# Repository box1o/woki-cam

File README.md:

# woki cam

modular infrared camera for optical tracking of retroreflective markers.

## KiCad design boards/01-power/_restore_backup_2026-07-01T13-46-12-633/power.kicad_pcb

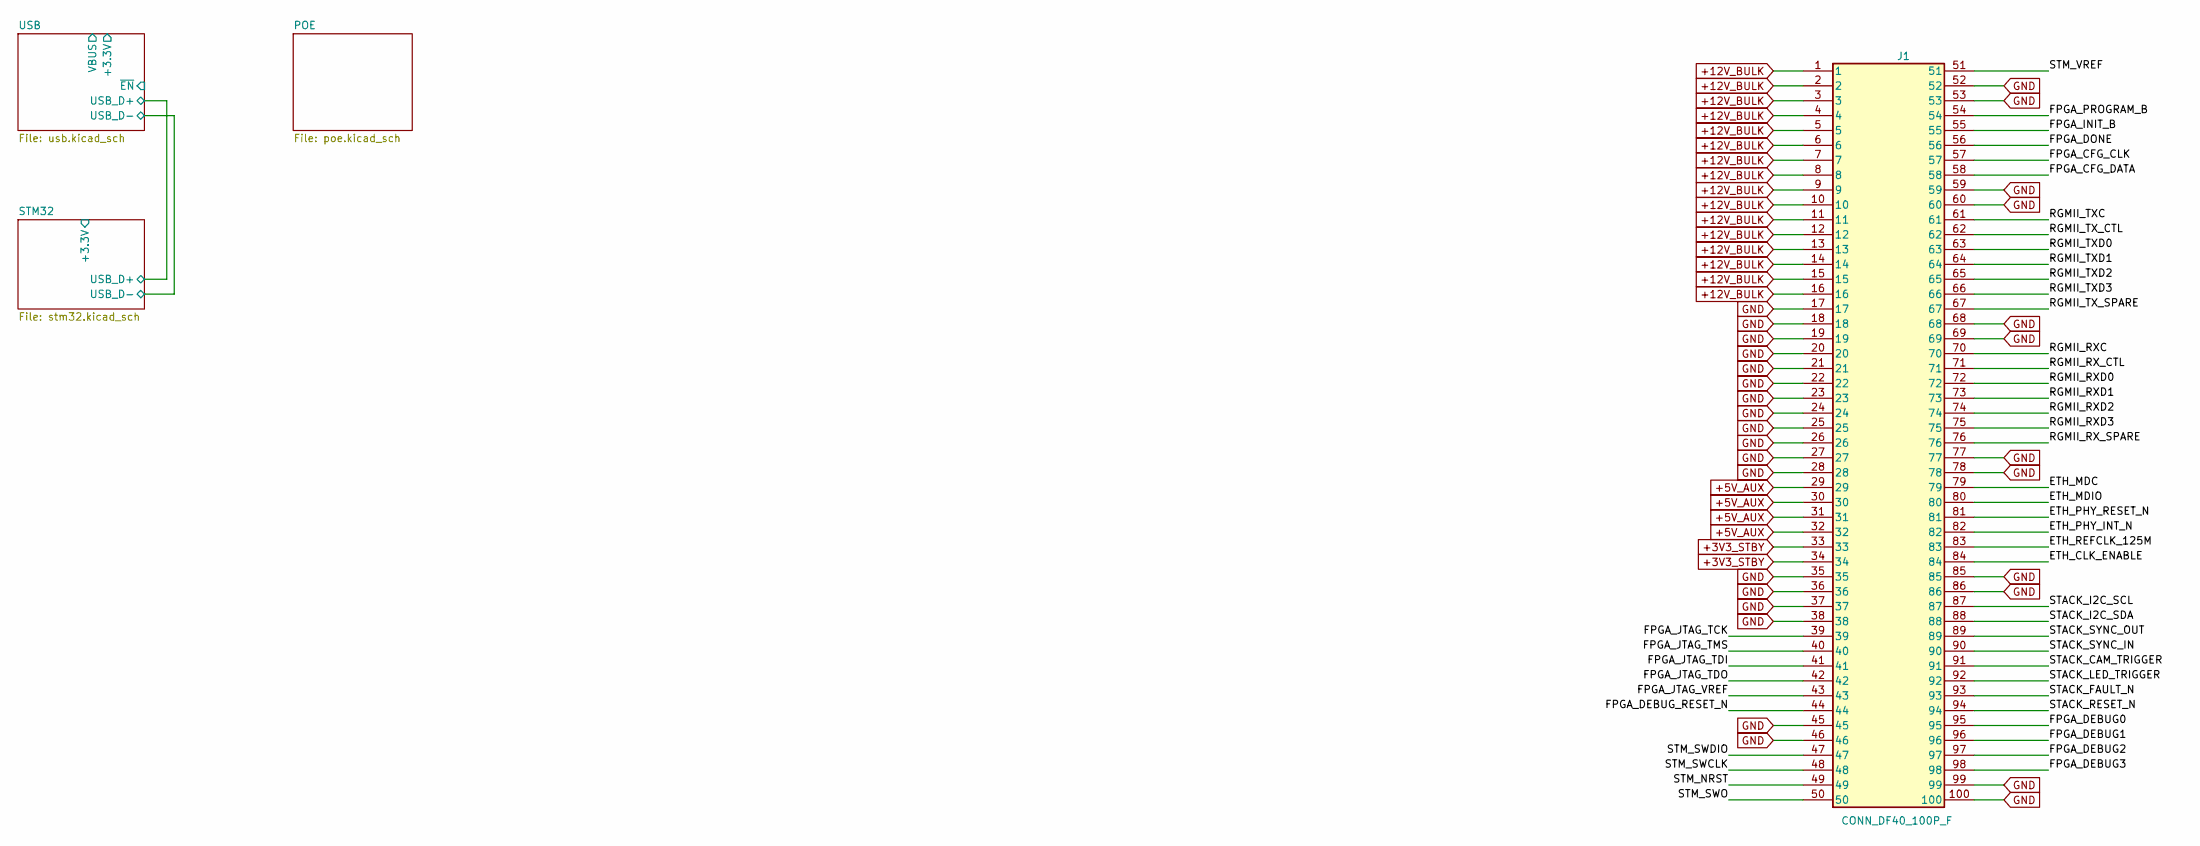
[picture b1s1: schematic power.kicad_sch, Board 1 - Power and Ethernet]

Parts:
J1: CONN_DF40_100P_F

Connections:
+3V3_STBY: J1.33, J1.34
+5V_AUX: J1.29, J1.30, J1.31, J1.32
+12V_BULK: J1.1, J1.2, J1.3, J1.4, J1.5, J1.6, J1.7, J1.8, J1.9, J1.10, J1.11, J1.12, J1.13, J1.14, J1.15, J1.16
/ETH_CLK_ENABLE: J1.84
/ETH_MDC: J1.79
/ETH_MDIO: J1.80
/ETH_PHY_INT_N: J1.82
/ETH_PHY_RESET_N: J1.81
/ETH_REFCLK_125M: J1.83
/FPGA_CFG_CLK: J1.57
/FPGA_CFG_DATA: J1.58
/FPGA_DEBUG0: J1.95
/FPGA_DEBUG1: J1.96
/FPGA_DEBUG2: J1.97
/FPGA_DEBUG3: J1.98
/FPGA_DEBUG_RESET_N: J1.44
/FPGA_DONE: J1.56
/FPGA_INIT_B: J1.55
/FPGA_JTAG_TCK: J1.39
/FPGA_JTAG_TDI: J1.41
/FPGA_JTAG_TDO: J1.42
/FPGA_JTAG_TMS: J1.40
/FPGA_JTAG_VREF: J1.43
/FPGA_PROGRAM_B: J1.54
/RGMII_RXC: J1.70
/RGMII_RXD0: J1.72
/RGMII_RXD1: J1.73
/RGMII_RXD2: J1.74
/RGMII_RXD3: J1.75
/RGMII_RX_CTL: J1.71
/RGMII_RX_SPARE: J1.76
/RGMII_TXC: J1.61
/RGMII_TXD0: J1.63
/RGMII_TXD1: J1.64
/RGMII_TXD2: J1.65
/RGMII_TXD3: J1.66
/RGMII_TX_CTL: J1.62
/RGMII_TX_SPARE: J1.67
/STACK_CAM_TRIGGER: J1.91
/STACK_FAULT_N: J1.93
/STACK_I2C_SCL: J1.87
/STACK_I2C_SDA: J1.88
/STACK_LED_TRIGGER: J1.92
/STACK_RESET_N: J1.94
/STACK_SYNC_IN: J1.90
/STACK_SYNC_OUT: J1.89
/STM_NRST: J1.49
/STM_SWCLK: J1.48
/STM_SWDIO: J1.47
/STM_SWO: J1.50
/STM_VREF: J1.51
GND: J1.17, J1.18, J1.19, J1.20, J1.21, J1.22, J1.23, J1.24, J1.25, J1.26, J1.27, J1.28, J1.35, J1.36, J1.37, J1.38, J1.45, J1.46, J1.52, J1.53, J1.59, J1.60, J1.68, J1.69, J1.77, J1.78, J1.85, J1.86, J1.99, J1.100; also elsewhere on the board

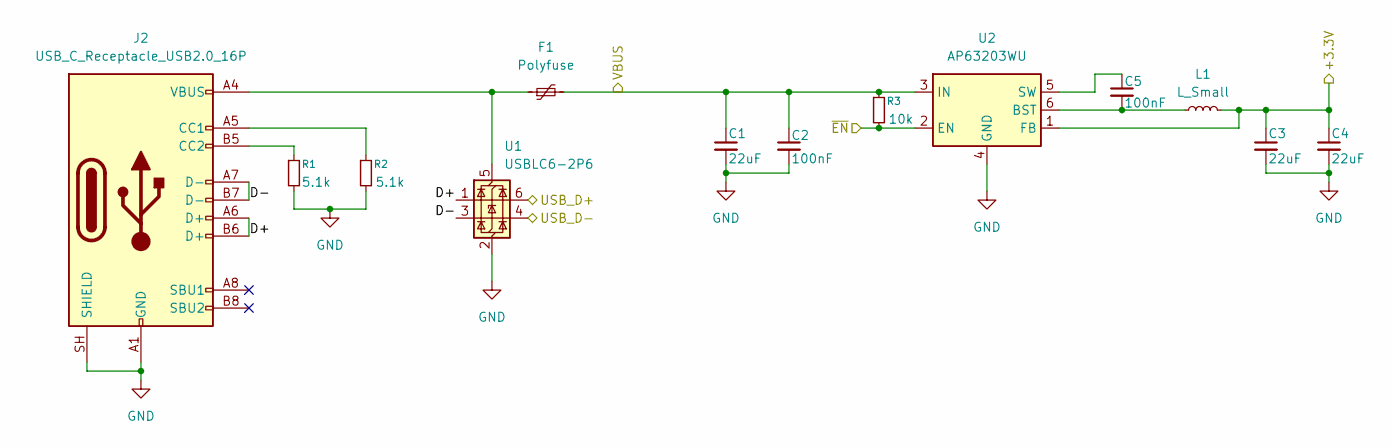
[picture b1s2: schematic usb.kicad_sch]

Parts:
C1, C3, C4: 22uF; C_0603_1608Metric
C2, C5: 100nF; C_0603_1608Metric
F1: Polyfuse; Fuse_0603_1608Metric
J2: USB_C_Receptacle_USB2.0_16P; CONN_USB_C_M
L1: L_Small; L_APV_ANR3012
R1, R2: 5.1k; R_0603_1608Metric
R3: 10k; R_0603_1608Metric
U1: USBLC6-2P6; SOT-666
U2: AP63203WU; TSOT-23-6

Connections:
/STM32/USB_D+: U1.6 (I/O1); also elsewhere on the board
/STM32/USB_D-: U1.4 (I/O2); also elsewhere on the board
/USB/+3.3V: C3.1, C4.1, L1.2, U2.1 (FB)
/USB/D+: J2.A6 (D+), J2.B6 (D+), U1.1 (I/O1)
/USB/D-: J2.A7 (D-), J2.B7 (D-), U1.3 (I/O2)
/USB/VBUS: C1.1, C2.1, F1.2, R3.1, U2.3 (IN)
/USB/~EN: R3.2, U2.2 (EN)
GND: C1.2, C2.2, C3.2, C4.2, J2.A1 (GND), J2.A12 (GND), J2.B1 (GND), J2.B12 (GND), J2.SH (SHIELD), R1.2, R2.2, U1.2 (GND), U2.4 (GND); also elsewhere on the board
unnamed: J2.A5 (CC1), R2.1
unnamed: J2.B5 (CC2), R1.1
unnamed: F1.1, J2.A4 (VBUS), J2.A9 (VBUS), J2.B4 (VBUS), J2.B9 (VBUS), U1.5 (VBUS)
unnamed: C5.2, L1.1, U2.6 (BST)
unnamed: C5.1, U2.5 (SW)

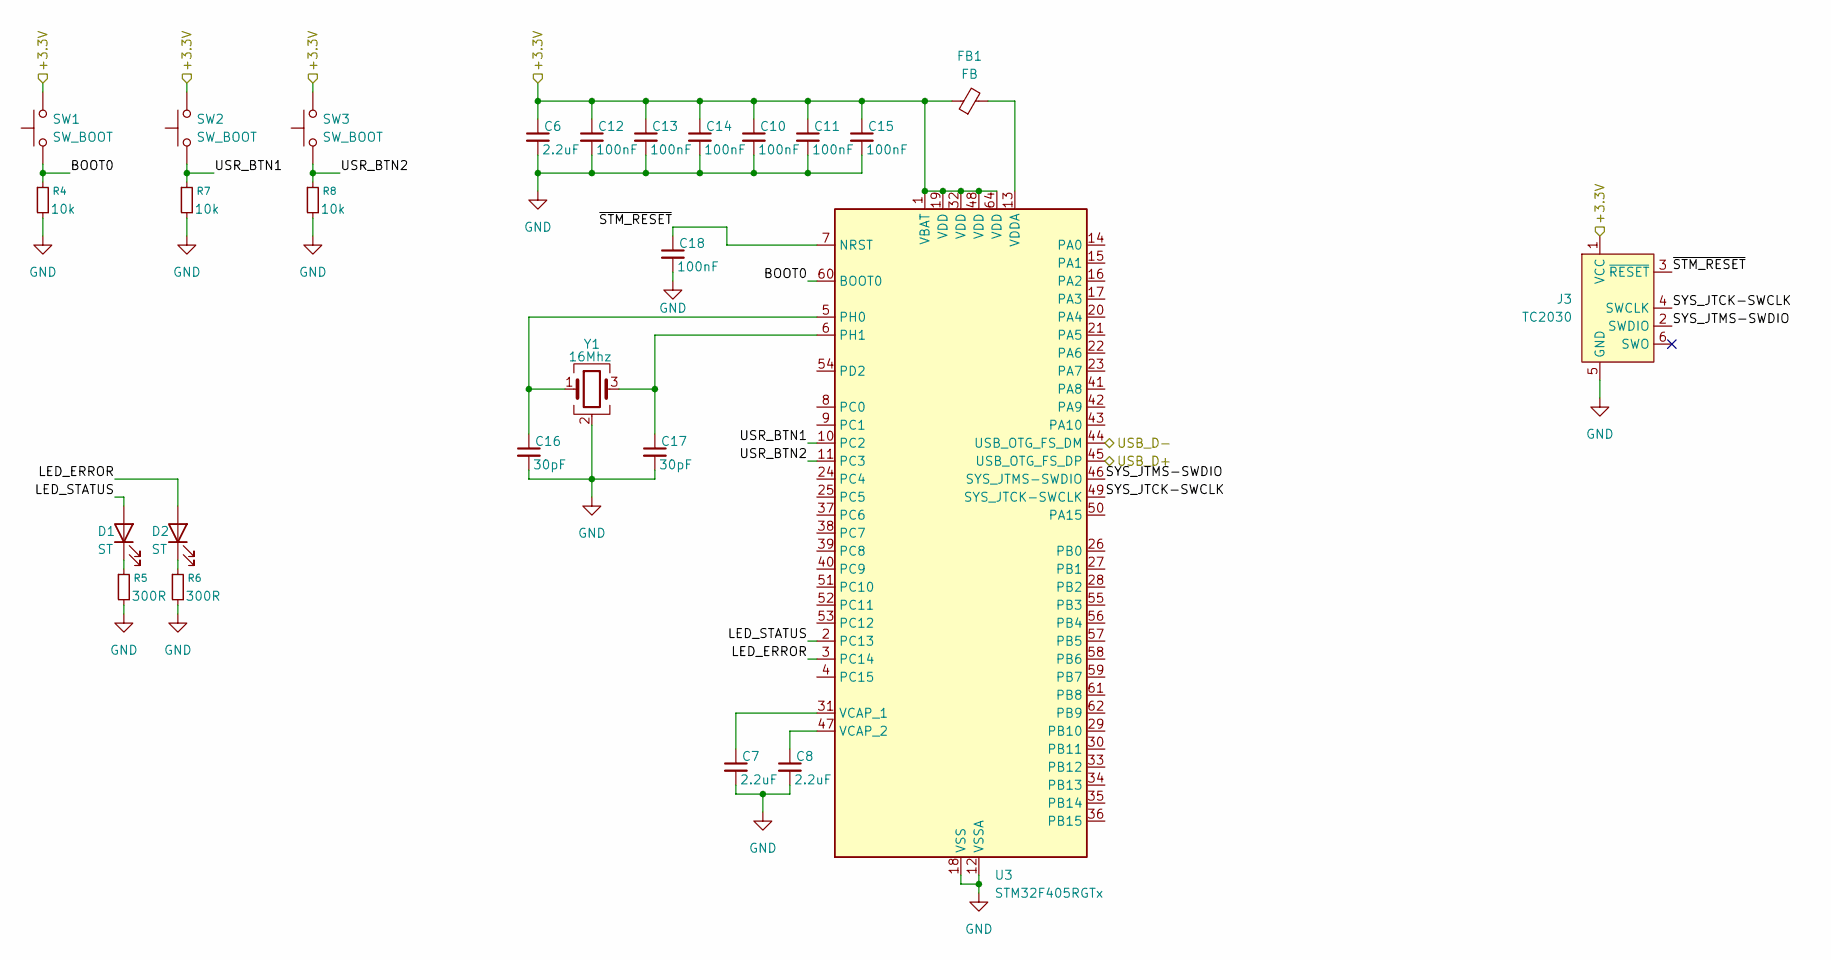
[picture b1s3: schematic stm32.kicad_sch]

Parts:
C6, C7, C8: 2.2uF; C_0603_1608Metric
C10, C11, C12, C13, C14, C15, C18: 100nF; C_0603_1608Metric
C16, C17: 30pF; C_0603_1608Metric
D1, D2: ST; LED_0603_1608Metric
FB1: FB; L_0603_1608Metric
J3: TC2030; Tag-Connect_TC2030-IDC-FP_2x03_P1.27mm_Vertical
R4, R7, R8: 10k; R_0603_1608Metric
R5, R6: 300R; R_0603_1608Metric
SW1, SW2, SW3: SW_BOOT; SW_B3U_1000P
U3: STM32F405RGTx; LQFP-64_10x10mm_P0.5mm
Y1: 16Mhz; Crystal_SMD_3225-4Pin_3.2x2.5mm

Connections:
/STM32/+3.3V: C6.1, C10.1, C11.1, C12.1, C13.1, C14.1, C15.1, FB1.1, J3.1 (VCC), SW1.2, SW2.2, SW3.2, U3.1 (VBAT), U3.19 (VDD), U3.32 (VDD), U3.48 (VDD), U3.64 (VDD)
/STM32/BOOT0: R4.1, SW1.1, U3.60 (BOOT0)
/STM32/LED_ERROR: D2.2 (A), U3.3 (PC14)
/STM32/LED_STATUS: D1.2 (A), U3.2 (PC13)
/STM32/SYS_JTCK-SWCLK: J3.4 (SWCLK), U3.49 (SYS_JTCK-SWCLK)
/STM32/SYS_JTMS-SWDIO: J3.2 (SWDIO), U3.46 (SYS_JTMS-SWDIO)
/STM32/USB_D+: U3.45 (USB_OTG_FS_DP); also elsewhere on the board
/STM32/USB_D-: U3.44 (USB_OTG_FS_DM); also elsewhere on the board
/STM32/USR_BTN1: R7.1, SW2.1, U3.10 (PC2)
/STM32/USR_BTN2: R8.1, SW3.1, U3.11 (PC3)
/STM32/~STM_RESET: C18.1, J3.3 (~RESET), U3.7 (NRST)
GND: C6.2, C7.2, C8.2, C10.2, C11.2, C12.2, C13.2, C14.2, C15.2, C16.2, C17.2, C18.2, J3.5 (GND), R4.2, R5.2, R6.2, R7.2, R8.2, U3.12 (VSSA), U3.18 (VSS), U3.63 (VSS), Y1.2 (G), Y1.4 (G); also elsewhere on the board
unnamed: D1.1 (K), R5.1
unnamed: D2.1 (K), R6.1
unnamed: C16.1, U3.5 (PH0), Y1.1
unnamed: C17.1, U3.6 (PH1), Y1.3
unnamed: C7.1, U3.31 (VCAP_1)
unnamed: C8.1, U3.47 (VCAP_2)
unnamed: FB1.2, U3.13 (VDDA)

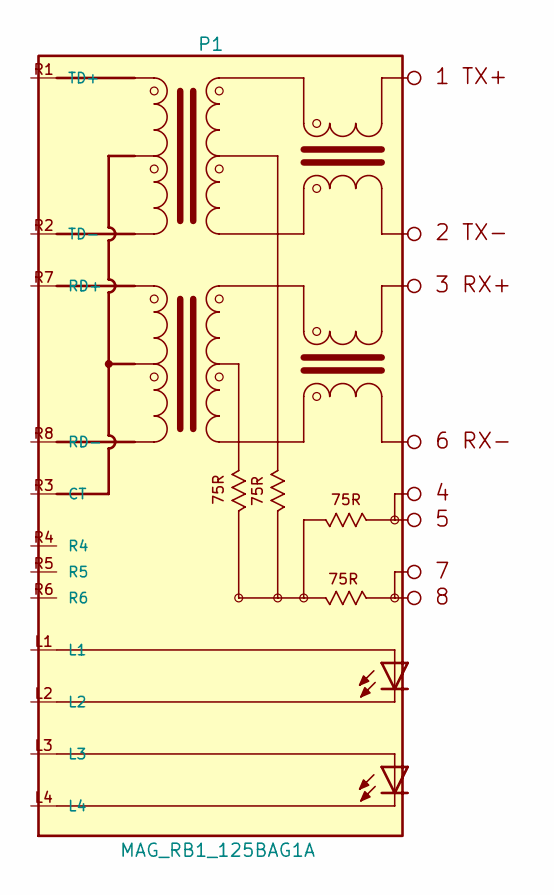
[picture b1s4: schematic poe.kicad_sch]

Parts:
P1: MAG_RB1_125BAG1A

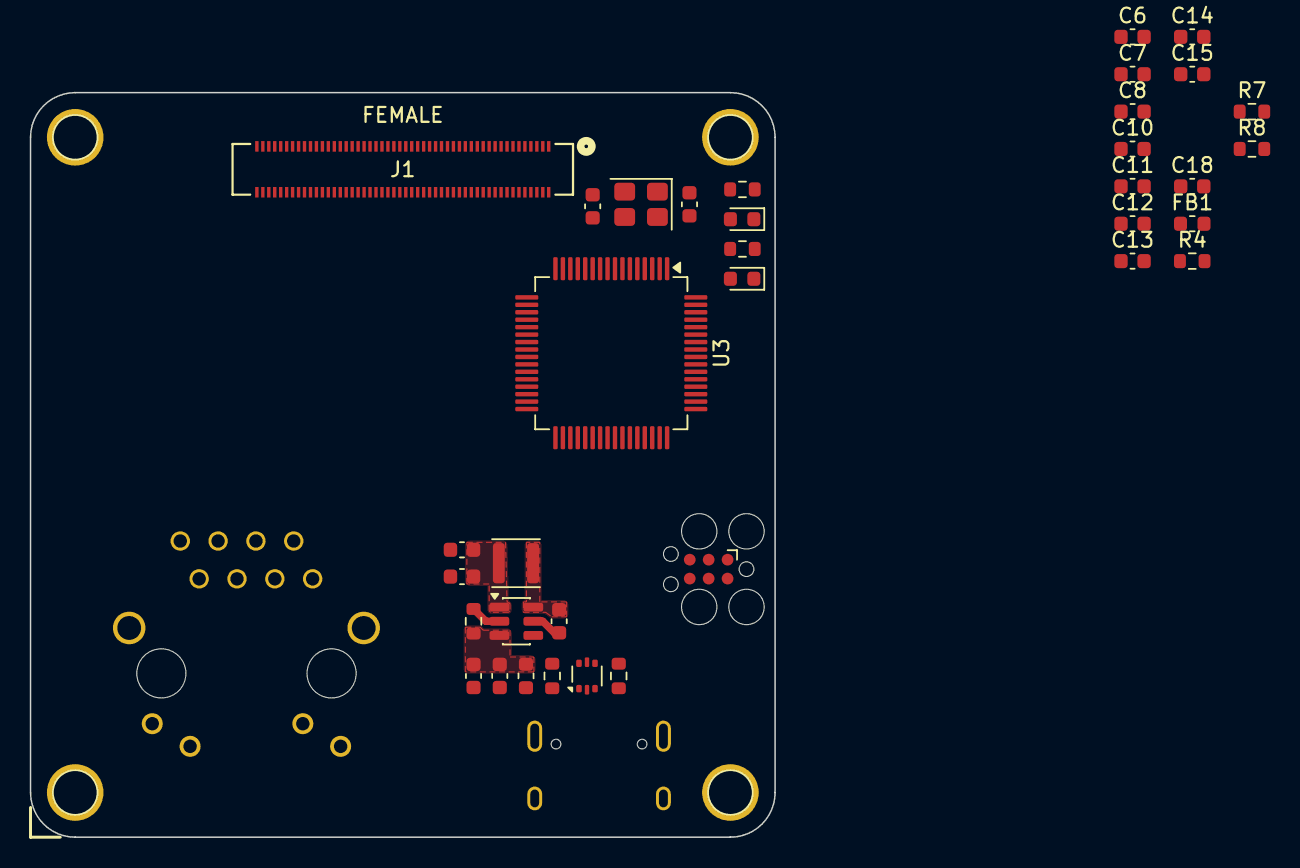
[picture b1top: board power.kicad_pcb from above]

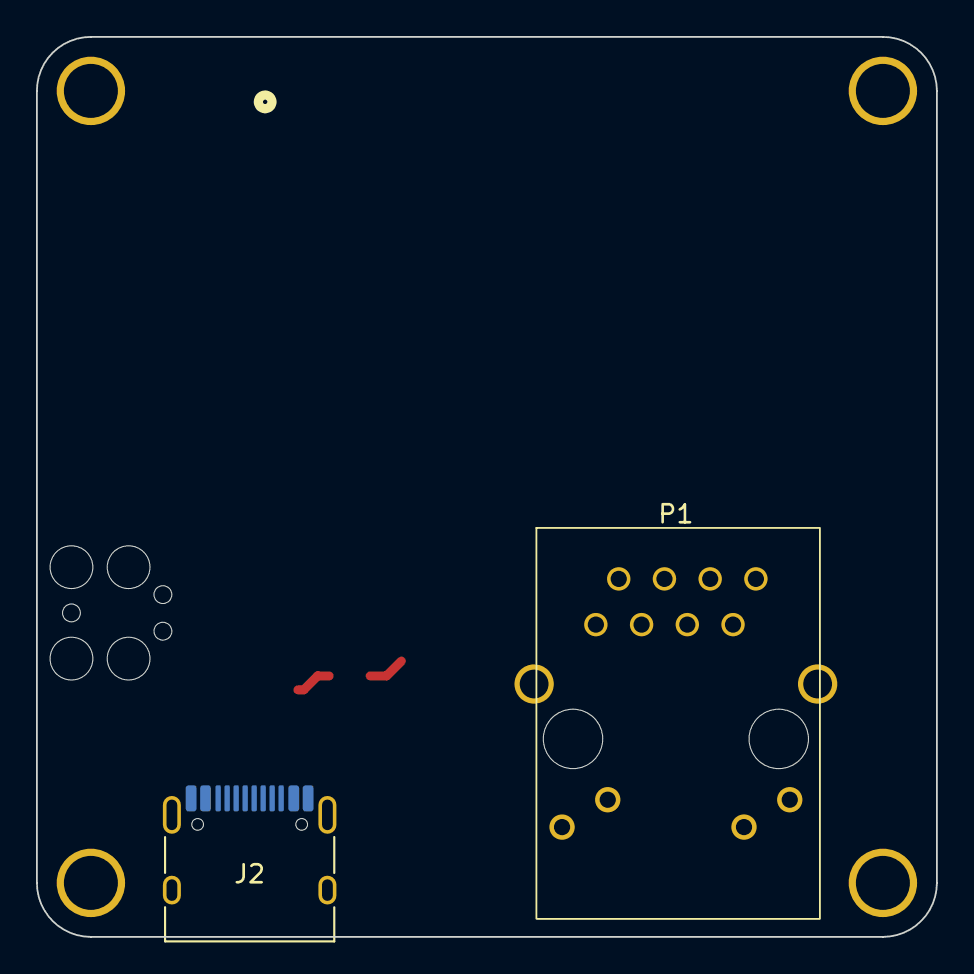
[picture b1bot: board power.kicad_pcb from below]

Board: 6 copper layers, 50.0 x 50.0 mm, 42 parts (2 on the bottom side), 32 nets.

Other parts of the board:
H1, H2, H3, H4: MNT_HOLE_M3

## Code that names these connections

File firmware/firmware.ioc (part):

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Mcu.Name=STM32F405RGTx
Mcu.Package=LQFP64
Mcu.UserName=STM32F405RGTx
PA11.Mode=Host_Only
PA11.Signal=USB_OTG_FS_DM
PA12.Mode=Host_Only
PA12.Signal=USB_OTG_FS_DP
PA13.Mode=Serial_Wire
PA13.Signal=SYS_JTMS-SWDIO
PA14.Mode=Serial_Wire
PA14.Signal=SYS_JTCK-SWCLK
PC13-ANTI_TAMP.GPIOParameters=GPIO_Label
PC13-ANTI_TAMP.GPIO_Label=LED_STATUS
PC13-ANTI_TAMP.Signal=GPIO_Output
PC14-OSC32_IN.GPIOParameters=GPIO_Label
PC14-OSC32_IN.GPIO_Label=LED_ERROR
PC14-OSC32_IN.Signal=GPIO_Output
PC2.GPIOParameters=GPIO_Label
PC2.GPIO_Label=USR_BTN1
PC2.Signal=GPIO_Input
PC3.GPIOParameters=GPIO_Label
PC3.GPIO_Label=USR_BTN2
PC3.Signal=GPIO_Input
PH0-OSC_IN.Mode=HSE-External-Oscillator
PH0-OSC_IN.Signal=RCC_OSC_IN
PH1-OSC_OUT.Mode=HSE-External-Oscillator
PH1-OSC_OUT.Signal=RCC_OSC_OUT
RCC.HSE_VALUE=16000000
RCC.SYSCLKFreq_VALUE=72000000
RCC.SYSCLKSource=RCC_SYSCLKSOURCE_PLLCLK
board=custom

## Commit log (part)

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2026-06-15 init: scaffold prj/ci
2026-06-16 feat: labels
2026-06-16 Update connector pinout
2026-06-16 feat: reference
2026-06-30 fix release collage outputs
